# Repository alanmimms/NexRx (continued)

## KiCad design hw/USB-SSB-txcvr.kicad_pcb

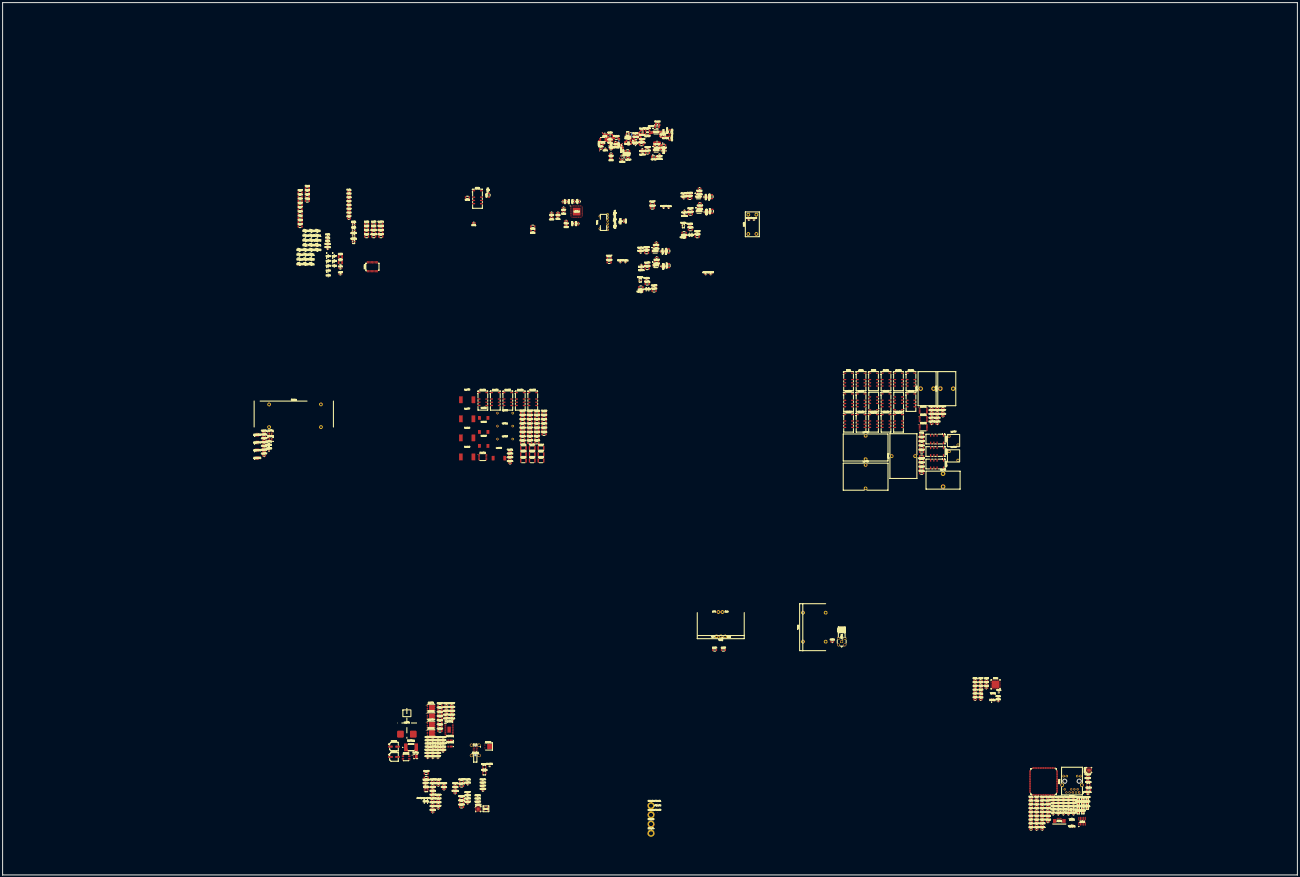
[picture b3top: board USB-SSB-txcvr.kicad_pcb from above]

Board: 6 copper layers, 1022.4 x 688.8 mm, 592 parts (0 on the bottom side), 441 nets.

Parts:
C201, C211, C1604, C1705, C2106, C2108: 100nF; C_0805_2012Metric
C202, C204, C205, C306, C308, C311, C313, C501, C1601, C1602, C1603, C1701, C1702, C1703, C1704, C1816, C1817, C1820, C1821, C2005, C2101, C2102, C2103, C2104, C2105, C2107, C2406: 10uF; C_0805_2012Metric
C203: 100uF; C_0805_2012Metric
C206, C207, C208, C210, C212, C214, C217, C218, C219, C220, C221, C222, C224, C225, C303, C307, C309, C310, C312, C314, C315, C316, C318, C321, C602, C608, C609, C613, C615, C1202, C1212, C1213, C1302, C1312, C1313, C1402, C1412, C1413, C1803, C1814, C1815, C2003, C2007, C2008, C2012, C2301, C2302, C2403, C2407, C2408, C2409, C2410, C2411: 0.1uF; C_0805_2012Metric
C209, C216, C223, C304, C320, C401, C402, C408, C410, C412, C413, C415, C417, C601, C603, C604, C1806, C1811, C1812, C1813, C1818, C1819, C2307, C2404: 1uF; C_0805_2012Metric
C213, C215, C302, C305, C2303, C2304: 2.2uF; C_0805_2012Metric
C301: 1uF 250V; C_1206_3216Metric
C317, C319, C605, C607, C612, C614, C2006, C2111, C2112: 4.7uF; C_0805_2012Metric
C403: 4pF; C_1206_3216Metric
C404: 8pF; C_1206_3216Metric
C405: 16pF; C_1206_3216Metric
C406: 32pF; C_1206_3216Metric
C407: 64pF; C_1206_3216Metric
C409: 128pF; C_1206_3216Metric
C411: 256pF; C_1206_3216Metric
C414: 512pF; C_1206_3216Metric
C416: 1024pF; C_1206_3216Metric
C418: 2048pF; C_1206_3216Metric
C419, C420, C1204, C1205, C1207, C1208, C1209, C1210, C1304, C1305, C1307, C1308, C1309, C1310, C1404, C1405, C1407, C1408, C1409, C1410, C2017, C2018, C2019, C2020, C2022: 1uF; C_1206_3216Metric
C421: 2.2nF; C_1206_3216Metric
C502: 10uF 500V; C_0805_2012Metric
C606: .1uF; C_0805_2012Metric
C610, C2001: 10nF; C_0805_2012Metric
C611: 1nF; C_0805_2012Metric
C701, C1201, C1301, C1401, C2021, C2023: 10uF; C_1206_3216Metric
C1203, C1206, C1211, C1214, C1303, C1306, C1311, C1314, C1403, C1406, C1411, C1414: 2.2uF; C_1206_3216Metric
C1215, C1216, C1217, C1218, C1315, C1316, C1317, C1318, C1415, C1416, C1417, C1418: 3.3nF; C_1206_3216Metric
C1605, C1633: 39pF; C_1206_3216Metric
C1606, C1611, C1621, C1632: 150pF; C_1206_3216Metric
C1607, C1634: 75pF; C_1206_3216Metric
C1608, C1619, C1622, C1631: 27pF; C_1206_3216Metric
C1609, C1630: 360pF; C_1206_3216Metric
C1610, C1620: 330pF; C_1206_3216Metric
C1612, C1629: 62pF; C_1206_3216Metric
C1613, C1628: 33pF; C_1206_3216Metric
C1614, C1626: 24pF; C_1206_3216Metric
C1615, C1623: 300pF; C_1206_3216Metric
C1616, C1624: 120pF; C_1206_3216Metric
C1617, C1627: 68pF; C_1206_3216Metric
C1618, C1625: 36pF; C_1206_3216Metric
C1801: 4.7uF 50V; C_0805_2012Metric
C1802: 0.1uF 50V; C_0805_2012Metric
C1804, C1805: 22uF; C_0805_2012Metric
C1807, C1808, C1809, C1810: 1uF 50V; C_0805_2012Metric
C2002, C2011: 100pF; C_0603_1608Metric
C2004, C2305, C2306: 3.3nF; C_0805_2012Metric
C2009, C2010: 0.22uF; C_0603_1608Metric
C2013: 220pF; C_0805_2012Metric
C2014, C2015: 10uF; CP_Elec_6.3x5.4
C2016: 470pF; C_0805_2012Metric
C2109: 4.7uF 50V; C_1206_3216Metric
C2110: 1280pF; C_1206_3216Metric
C2113: 640pF; C_1206_3216Metric
C2114: 320pF; C_1206_3216Metric
C2115: 0.1uF 50V; C_1206_3216Metric
C2116: 160pF; C_1206_3216Metric
C2117: 80pF; C_1206_3216Metric
C2118: 40pF; C_1206_3216Metric
C2119: 20pF; C_1206_3216Metric
C2120: 10pF; C_1206_3216Metric
C2121: 5pF; C_1206_3216Metric
C2401, C2402: 8.2pF; C_0603_1608Metric
C2405: 470pF; C_1206_3216Metric
C2412: 1000pF; C_0805_2012Metric
CF1801: 1uF; C_0805_2012Metric
D301: STS321150B100AH; Infineon_SG-WLL-2-3_0.58x0.28_P0.36mm
D2001, D2002: DFLS1200-7; DFLS12007
D2101: MMQA33VT1G; SC-74-6_1.55x2.9mm_P0.95mm
FB301: 600; L_0603_1608Metric
FB2401: BLM21AG102SN1D; L_0805_2012Metric
FID101, FID102, FID103: Fiducial; Fiducial_0.5mm_Mask2mm
IC2001: LTC3779IFE#PBF; SOP50P640X120-39N
J201: 68710814022
J202: FTSH-105-01-L-DV-K; FTSH10501LDVK
J501: SMA; RFPCSMA27F
J2101: Amphenol 10167129; 1016712900011LF
J2401: RJ45_Abracon_ARJP11A-MASA-B-A-EMU2; RJ45_Abracon_ARJP11A-MA_Horizontal
K501, K701, K702, K703, K1601, K1602, K1603, K1604, K1605, K1701, K1702, K1703, K1704, K1705, K1706, K1707, K1708, K2101, K2102, K2103, K2104, K2105, K2106, K2107, K2108, K2109: G6S-2G; Relay_DPDT_Omron_G6S-2G
L301: 1.2uH; L_0805_2012Metric
L401: 8t bifilar; L_CommonMode_Toroid_Vertical_L19.3mm_W10.8mm_Px6.35mm_Py15.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
L402: 8.2uH; L_1210_3225Metric
L403: 2.7uH; L_1210_3225Metric
L404: 820nH; L_0805_2012Metric
L405: 270nH; L_0805_2012Metric
L1601, L1604, L1616, L1620: 1.2uH; L_1812_4532Metric
L1602, L1618: 3.3uH; L_Wurth_8.4mm_sq_SMT
L1603, L1607, L1614, L1619: 3.9uH; L_Wurth_12.1mm_sq_SMT
L1605, L1615: 17.4uH; toroid-inductor-t80-2
L1606, L1610, L1617: 1.5uH; L_1812_4532Metric
L1608, L1613: 1uH; L_1812_4532Metric
L1609: 8.2uH; L_Wurth_10.9mm_sq_SMT
L1611: 19.1uH; toroid-inductor-t80-2
L1612: 4.7uH; L_Wurth_8.4mm_sq_SMT
L1701: 64uH; L_Toroid_Vertical_L35.1mm_W21.1mm_P18.50mm_Vishay_TJ6
L1702: 32uH; L_Toroid_Vertical_L35.1mm_W21.1mm_P18.50mm_Vishay_TJ6
L1703: 16uH; L_Toroid_Vertical_L35.1mm_W21.1mm_P18.50mm_Vishay_TJ6
L1704: 8uH; L_Toroid_Vertical_L26.7mm_W14.0mm_P10.16mm_Pulse_D
L1705: 4uH; L_Toroid_Vertical_L26.7mm_W14.0mm_P10.16mm_Pulse_D
L1706: 2uH; L_Toroid_Vertical_L26.7mm_W14.0mm_P10.16mm_Pulse_D
L1707: 1uH; Coilcraft-uni10
L1708: 0.5uH; Coilcraft-uni10
L1801: 2.2uH; IND_XGL4030_COC
L1802: 2.2uH; L_0805_2012Metric
L1803: 3.3uH; L_0805_2012Metric
L2001: 6.8uH; Bourns PQ2614BLA-6R8K
MH101, MH102, MH103, MH104: MountingHole; MountingHole_3.2mm_M3_ISO7380_Pad
Q801, Q901, Q1001, Q1101: 2N7002K; SOT-23
Q2001, Q2002, Q2003, Q2004: BSC360N15NS3 G; Infineon_PG-TDSON-8_6.15x5.15mm
Q2101: SQJ433EP; PowerPAK_SO-8L_Single
Q2301, Q2302: EPC2037; EPC_BGA-4_0.9x0.9mm_Layout2x2_P0.45mm
Q2303, Q2304, Q2305, Q2306: IGB110S101XTMA1
R201, R202, R203, R204, R205, R206, R207, R208, R210, R303, R304, R801, R901, R1001, R1101, R1201, R1202, R1203, R1204, R1205, R1206, R1207, R1208, R1301, R1302, R1303, R1304, R1305, R1306, R1307, R1308, R1401, R1402, R1403, R1404, R1405, R1406, R1407, R1408, R2002, R2005, R2008, R2108, R2401, R2406, R2408, R2409, R2410, R2420: 10k; R_0603_1608Metric
R209, R602, R2015, R2016, R2019, R2020, R2104: 100; R_0603_1608Metric
R301, R302, R2012, R2013, R2101, R2106: 1k; R_0603_1608Metric
R401: 6.8; R_0603_1608Metric
R501: 49.9; R_1206_3216Metric
R502, R504: 47k; R_1206_3216Metric
R503, R505: 220; R_1206_3216Metric
R601, R1805, R1806, R2411, R2412: 0; R_0603_1608Metric
R802, R804, R902, R904, R1002, R1004, R1102, R1104: 34; R_1206_3216Metric
R803, R903, R1003, R1103: 562; R_1206_3216Metric
R1209, R1210, R1211, R1212, R1309, R1310, R1311, R1312, R1409, R1410, R1411, R1412: 330; R_0603_1608Metric
R1801: 60.4k; R_0603_1608Metric
R1802, R2415: 12.1k; R_0603_1608Metric
R1803, R1804, R1811, R1812, R1813, R1814, R2105: 0; R_1206_3216Metric
R1807, R1809, R2003, R2009, R2102, R2107, R2407: 100k; R_0603_1608Metric
R1808: 22.1k; R_0603_1608Metric
R1810: 13.7k; R_0603_1608Metric
R2001: 649k; R_0603_1608Metric
R2004, R2010: 3.53k; R_0603_1608Metric
R2006: 13k; R_0603_1608Metric
R2007: 125k; R_0603_1608Metric
R2011: 107k; R_0603_1608Metric
R2014: 5; R_0603_1608Metric
R2017, R2018, R2022, R2023: 2; R_0603_1608Metric
R2021: 5m; CSS2H3920K5L00F
R2103: 22k; R_0603_1608Metric
R2402, R2403, R2404, R2405: 33; R_0603_1608Metric
R2413, R2414, R2416, R2417: 49.9; R_0603_1608Metric
R2418, R2419: 270; R_0805_2012Metric
T301: 12t primary : 6T #26 trifilar secondary FT37-43; Toroid-1pri-3sec-ft50
T501: 2xFT140-stacked-bruene
T502: 16t:8t bifilar #18AWG FT140-43; 2xFT140-stacked
T2301: 2xFT240-stacked
TP201: PG0; TestPoint_Pad_1.5x1.5mm
TP202: PG1; TestPoint_Pad_1.5x1.5mm
TP203: PG2; TestPoint_Pad_1.5x1.5mm
TP204: PG3; TestPoint_Pad_1.5x1.5mm
TP205: PG4; TestPoint_Pad_1.5x1.5mm
TP206: PG5; TestPoint_Pad_1.5x1.5mm
TP207: PG6; TestPoint_Pad_1.5x1.5mm
TP208: PG7; TestPoint_Pad_1.5x1.5mm
TP209: PG8; TestPoint_Pad_1.5x1.5mm
TP210: PG14; TestPoint_Pad_1.5x1.5mm
TP211: PG15; TestPoint_Pad_1.5x1.5mm
U201: STM32H753ZIT6; LQFP-144_20x20mm_P0.5mm
U301: OPA1692xDGK; VSSOP-8_3x3mm_P0.65mm
U302, U303, U304, U410, U411, U412, U413, U414, U415, U416, U417, U418, U419, U420, U421, U422, U423, U424, U425, U426, U801, U802, U901, U902, U1001, U1002, U1101, U1102: AS183-92LF; SOT65P220X110-6N
U305: SOT65P220X110-6N
U306: AK5578EN; QFN50P900X900X100-65N
U401: MCP23S17_SS; SSOP-28_5.3x10.2mm_P0.65mm
U402, U403, U404, U405, U406, U407, U408, U409: 74LVC2G04; DCK6
U601: TPS7A2025PDQN; Texas_X2SON-4_1x1mm_P0.65mm
U602: ICE40UP5K-SG48ITR; QFN-48-1EP_7x7mm_P0.5mm_EP5.6x5.6mm
U1201, U1301, U1401: SZNUP1105LT1G; SOT-23
U1202, U1302, U1402: TS3A4751RUCR; TS3A4751-RUC14
U1203, U1204, U1303, U1304, U1403, U1404: MAX9939AUB+T; 21-0061L_MXM
U1601, U1701, U2101, U2102: TLC6C598PW; TSSOP-16_4.4x5mm_P0.65mm
U1801: LMR43610R3RPER; RPE0009A-MFG
U1802: TPS7A2012DQN; Texas_X2SON-4_1x1mm_P0.65mm
U1803, U1804: LMR51430; SOT-23-6
U1805: TPS7A92050DBVR; Texas_X2SON-4_1x1mm_P0.65mm
U1806: TPS7A2033DQN; Texas_X2SON-4_1x1mm_P0.65mm
U2001: NVTFS6H888NLTAG; WDFN_8NLTAG_ONS
U2002: TLV9062xD; SOIC-8_3.9x4.9mm_P1.27mm
U2103: STUSB4500QTR; QFN-24-1EP_4x4mm_P0.5mm_EP2.7x2.7mm
U2301, U2302: LMG1210RVRR; RVR0019A
U2303: TMP110D; Texas_X2SON-5_0.8x0.8mm_P0.48mm
U2401: LAN8742A; VQFN-24-1EP_4x4mm_P0.5mm_EP2.5x2.5mm_ThermalVias
U2402: USBLC6-4SC6; SOT-23-6
X601: XC8102AA01NR-G; XC8102AA01NRG
Y201: ECS-2033-250-BN; ECS2033250BN
Y601: ECS-TXO-2016-33-400-TR; ECSTXO201633400TR
Y2401: ECS-250-8-37B2-RWN; ECS2033250BN

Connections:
+2.7V: C2112.1, U2103.23 (VREG_2V7)
+3.3V: C201.1, C202.1, C203.1, C204.1, C205.1, C206.1, C207.1, C208.1, C210.1, C212.1, C214.1, C216.1, C217.1, C218.1, C219.1, C220.1, C221.1, C222.1, C224.1, C315.1, C316.2, C317.2, C320.1, C321.1, C401.1, C402.1, C408.1, C410.1, C412.1, C413.1, C415.1, C417.1, C419.1, C420.1, C601.1, C602.1, C603.1, C1603.2, C1604.2, C1704.2, C1705.2, C1806.1, C2104.2, C2106.2, C2107.2, C2108.2, C2307.1, C2403.1, FB2401.1, J201.2, J201.8, J202.1 (VTref), R202.1, R203.1, R204.1, R205.1, R206.1, R207.1, R208.1, R601.1, R801.1, R901.1, R1001.1, R1101.1, R1805.1, R1806.1, R1813.1, R2005.1, R2108.1, R2406.2, R2407.2, R2408.2, R2409.2, R2410.2, U201.6 (VBAT), U201.17 (VDD), U201.30 (VDD), U201.39 (VDD), U201.52 (VDD), U201.62 (VDD), U201.72 (VDD), U201.84 (VDD), U201.95 (VDD33USB), U201.108 (VDD), U201.121 (VDD), U201.131 (VDD), U201.144 (VDD), U305.5 (V), U306.25 (TVDD), U306.30 (PW1), U306.31 (PW2), U306.32 (MSN), U306.51 (TDM0), U306.52 (TDM1), U306.54 (I2C), U306.57 (LDOE), U306.58 (ODP), U401.9 (VDD), U401.15 (A0), U402.5 (V), U403.5 (V), U404.5 (V), U405.5 (V), U406.5 (V), U407.5 (V), U408.5 (V), U409.5 (V), U601.4 (IN), U1601.1 (VCC), U1601.7 (~CLR), U1601.8 (~G), U1701.1 (VCC), U1701.7 (~CLR), U1701.8 (~G), U1802.4 (IN), U2101.1 (VCC), U2101.7 (~CLR), U2101.8 (~G), U2102.1 (VCC), U2102.7 (~CLR), U2102.8 (~G), U2303.5 (V+), U2401.9 (VDDIO), Y201.4 (VDD), Y601.4 (VDD)
+3.3VA: C223.1, C225.1, C1201.1, C1202.1, C1301.1, C1302.1, C1401.1, C1402.1, R301.2, R1812.1, U201.33 (VDDA), U1201.3, U1202.14 (V+), U1301.3, U1302.14 (V+), U1401.3, U1402.14 (V+)
+3.3VFPGAIO: C605.1, C606.1, C612.1, C613.1, C614.1, C615.1, U602.1 (VCCIO_2), U602.22 (SPI_VCCIO1), U602.33 (VCCIO_0), X601.3 (VOUT)
+5V: C501.1, C701.2, C1601.1, C1602.1, C1701.1, C1702.1, C1703.1, C2101.1, C2102.1, C2103.1, C2105.2, C2301.1, C2302.1, C2303.1, C2304.1, K501.12, K701.1, K702.1, K703.1, K1601.1, K1602.1, K1603.1, K1604.1, K1605.1, K1701.1, K1702.1, K1703.1, K1704.1, K1705.1, K1706.1, K1707.1, K1708.1, K2101.1, K2102.1, K2103.1, K2104.1, K2105.1, K2106.1, K2107.1, K2108.1, K2109.1, Q2301.2 (S), Q2301.4 (S), Q2302.2 (S), Q2302.4 (S), R1814.1, U2301.2 (VIN), U2301.4 (VCC), U2301.5 (DHL), U2301.6 (DLH), U2302.2 (VIN), U2302.4 (VCC), U2302.5 (DHL), U2302.6 (DLH)
+5VA: C309.1, C1209.1, C1210.1, C1212.1, C1213.1, C1309.1, C1310.1, C1312.1, C1313.1, C1409.1, C1410.1, C1412.1, C1413.1, C2001.1, C2003.1, C2005.1, R1811.1, U301.8 (V+), U306.2 (AVDD1), U306.15 (AVDD2), U1203.9 (VCC), U1204.9 (VCC), U1303.9 (VCC), U1304.9 (VCC), U1403.9 (VCC), U1404.9 (VCC), U2002.8 (V+)
+6V: C1812.1, C1813.1, R1803.1, U1805.4 (IN), U1806.4 (IN)
/FPGA/CDONE: U201.141 (PE0), U602.7 (CDONE)
/FPGA/Ctrl.audioReset: R210.1, U201.42 (PA6), U306.28 (PDN)
/FPGA/Ctrl.enable5V: U201.26 (PC0), U1804.5 (EN)
/FPGA/Ctrl.enable6V: U201.53 (PF13), U1801.3 (EN_UVLO)
/FPGA/Ctrl.qsdBCLK: U201.4 (PE5), U306.33 (BICK/DCLK)
/FPGA/Ctrl.qsdData: U201.5 (PE6), U306.36 (SDTO1/DSDOL2)
/FPGA/Ctrl.qsdMCLK: U306.24 (MCLK), U602.12 (IOB_22a)
/FPGA/Ctrl.qsdMOSI: U201.67 (PE14), U1203.2 (DIN), U1204.2 (DIN), U1303.2 (DIN), U1304.2 (DIN), U1403.2 (DIN), U1404.2 (DIN)
/FPGA/Ctrl.qsdNSS: U201.64 (PE11), U1203.10 (*CS), U1204.10 (*CS), U1303.10 (*CS), U1304.10 (*CS), U1403.10 (*CS), U1404.10 (*CS)
/FPGA/Ctrl.qsdPh0a: U602.6 (IOB_13b), U1402.1 (NO1)
/FPGA/Ctrl.qsdPh1a: U602.21 (IOB_23b), U1202.1 (NO1)
/FPGA/Ctrl.qsdPh2a: U602.45 (IOB_5b), U1302.1 (NO1)
/FPGA/Ctrl.qsdPh2b: U602.2 (IOB_6a), U602.9 (IOB_16a), U602.13 (IOB_24a), U1202.3 (NO2), U1302.3 (NO2), U1402.3 (NO2)
/FPGA/Ctrl.qsdPh2c: U602.4 (IOB_8a), U602.10 (IOB_18a), U602.20 (IOB_25b_G3), U1202.8 (NO3), U1302.8 (NO3), U1402.8 (NO3)
/FPGA/Ctrl.qsdPh2d: U602.3 (IOB_9b), U602.11 (IOB_20a), U602.19 (IOB_29b), U1202.11 (NO4), U1302.11 (NO4), U1402.11 (NO4)
/FPGA/Ctrl.qsdSCK: U201.1 (PE2), U1203.1 (SCLK), U1204.1 (SCLK), U1303.1 (SCLK), U1304.1 (SCLK), U1403.1 (SCLK), U1404.1 (SCLK)
/FPGA/Ctrl.qsdWCLK: U201.3 (PE4), U306.34 (LRCK/DSDOL1)
/FPGA/Ctrl.switchMOSI: U201.29 (PC3_C), U2101.2 (SER_IN)
/FPGA/Ctrl.switchRCK: U201.10 (PF0), U1601.10 (RCK), U1701.10 (RCK), U2101.10 (RCK), U2102.10 (RCK)
/FPGA/Ctrl.switchSCK: U201.69 (PB10), U1601.15 (SRCK), U1701.15 (SRCK), U2101.15 (SRCK), U2102.15 (SRCK)
/FPGA/Ctrl.tmpSCL: U201.136 (PB6), U2103.7 (SCL)
/FPGA/Ctrl.tmpSDA: U201.137 (PB7), U2103.8 (SDA)
/FPGA/Ctrl.txBCLK: U201.20 (PF8), U602.43 (IOT_49a)
/FPGA/Ctrl.txData: U201.2 (PE3), U602.42 (IOT_51a)
/FPGA/Ctrl.txMCLK: U201.19 (PF7), U602.36 (IOT_48b)
/FPGA/Ctrl.txWCLK: U201.21 (PF9), U602.38 (IOT_50b)
/FPGA/Ctrl.usbPOK2: U201.22 (PF10), U2103.20 (POWER_OK2)
/FPGA/Ctrl.usbPOK3: U201.49 (PF11), U2103.14 (POWER_OK3)
/FPGA/Ctrl.usbReset: R2107.1, U2103.6 (RESET)
/FPGA/Ctrl.usbnALERT: R2108.2, U201.54 (PF14), U2103.19 (ALERT)
/FPGA/PAI+: U602.25 (IOT_36b), U2301.18 (HI_EN)
/FPGA/PAI-: U602.23 (IOT_37a), U2301.19 (PWM_LI)
/FPGA/PAQ+: U602.27 (IOT_38b), U2302.18 (HI_EN)
/FPGA/PAQ-: U602.26 (IOT_39a), U2302.19 (PWM_LI)
/FPGA/STM32clock: U201.23 (PH0-OSC_IN), U602.18 (IOB_31b)
/Power/FPGA1V2enable: U201.142 (PE1), U1802.3 (EN)
/Power/Tx EER Envelope Buck-Boost/BG1: IC2001.1 (BG1), R2018.1
/Power/Tx EER Envelope Buck-Boost/BG2: IC2001.19 (BG2), R2023.1
/Power/Tx EER Envelope Buck-Boost/FB: C2011.2, IC2001.10 (VFB), R2011.2, U2002.1
/Power/Tx EER Envelope Buck-Boost/IAVGSNSN: C2016.2, R2019.1
/Power/Tx EER Envelope Buck-Boost/IAVGSNSP: C2016.1, IC2001.26 (IAVGSNSP), IC2001.28 (IAVGSNSN), R2020.1
/Power/Tx EER Envelope Buck-Boost/SENSEN: C2013.1, IC2001.12 (SENSEN), R2016.1
/Power/Tx EER Envelope Buck-Boost/SENSEP: C2013.2, IC2001.11 (SENSEP), R2015.1
/Power/Tx EER Envelope Buck-Boost/SW1: C2010.1, IC2001.38 (SW1), L2001.1, Q2001.1 (S), Q2001.2 (S), Q2001.3 (S), Q2002.5 (D)
/Power/Tx EER Envelope Buck-Boost/SW2: C2009.2, IC2001.20 (SW2), L2001.2, Q2003.1 (S), Q2003.2 (S), Q2003.3 (S), Q2004.5 (D)
/Power/Tx EER Envelope Buck-Boost/TG1: IC2001.37 (TG1), R2017.1
/Power/Tx EER Envelope Buck-Boost/TG2: IC2001.21 (TG2), R2022.1
/Power/TxAmplitude: R2008.1, U201.40 (PA4)
/Power/TxEnable: IC2001.24 (RUN), U201.103 (PA11)
/Power/TxPGOOD: IC2001.18 (PGOOD), R2005.2, U201.96 (PC6)
/Power/USB-PD/CC1: D2101.4 (K_3), J2101.A5 (CC1), U2103.1 (CC1DB), U2103.2 (CC1)
/Power/USB-PD/CC2: D2101.6 (K_4), J2101.B5 (CC2), U2103.4 (CC2), U2103.5 (CC2DB)
/Power/USB-PD/VBUS_DISCH: R2101.2, U2103.18 (VBUS_VS_DISCH)
/Power/scaledEERVdd: U201.50 (PF12), U2002.6 (-), U2002.7
/Rx Front End/Clipper, Attenuator, Preselector/C0: U401.21 (GPA0), U406.1, U410.4 (V1)
/Rx Front End/Clipper, Attenuator, Preselector/C1: U401.22 (GPA1), U406.3, U411.4 (V1)
/Rx Front End/Clipper, Attenuator, Preselector/C2: U401.23 (GPA2), U407.1, U412.4 (V1)
/Rx Front End/Clipper, Attenuator, Preselector/C3: U401.24 (GPA3), U407.3, U413.4 (V1)
/Rx Front End/Clipper, Attenuator, Preselector/C4: U401.25 (GPA4), U408.1, U414.4 (V1)
/Rx Front End/Clipper, Attenuator, Preselector/C5: U401.26 (GPA5), U408.3, U416.4 (V1)
/Rx Front End/Clipper, Attenuator, Preselector/C6: U401.27 (GPA6), U409.1, U417.4 (V1)
/Rx Front End/Clipper, Attenuator, Preselector/C7: U401.28 (GPA7), U409.3, U419.4 (V1)
/Rx Front End/Clipper, Attenuator, Preselector/C8: U401.1 (GPB0), U402.1, U422.4 (V1)
/Rx Front End/Clipper, Attenuator, Preselector/C9: U401.2 (GPB1), U402.3, U424.4 (V1)
/Rx Front End/Clipper, Attenuator, Preselector/C10: U401.3 (GPB2), U403.1, U426.4 (V1)
/Rx Front End/Clipper, Attenuator, Preselector/Ctrl.atten3dB: Q1101.1 (G), U1101.4 (V1), U1102.4 (V1)
/Rx Front End/Clipper, Attenuator, Preselector/Ctrl.atten6dB: Q801.1 (G), U801.4 (V1), U802.4 (V1)
/Rx Front End/Clipper, Attenuator, Preselector/Ctrl.atten12dB: Q901.1 (G), U901.4 (V1), U902.4 (V1)
/Rx Front End/Clipper, Attenuator, Preselector/Ctrl.atten24dB: Q1001.1 (G), U1001.4 (V1), U1002.4 (V1)
/Rx Front End/Clipper, Attenuator, Preselector/L1: U401.5 (GPB4), U404.1, U418.4 (V1)
/Rx Front End/Clipper, Attenuator, Preselector/L1L2: U401.4 (GPB3), U403.3, U415.4 (V1), U421.4 (V1)
/Rx Front End/Clipper, Attenuator, Preselector/L2: U401.6 (GPB5), U404.3, U420.4 (V1)
/Rx Front End/Clipper, Attenuator, Preselector/L3: U401.7 (GPB6), U405.1, U423.4 (V1)
/Rx Front End/Clipper, Attenuator, Preselector/L4: U401.8 (GPB7), U405.3, U425.4 (V1)
/Rx Front End/Clipper, Attenuator, Preselector/RxZ200: C301.2, D301.1 (A1), U1001.5 (J1)
/Rx Front End/Clipper, Attenuator, Preselector/Tpad 3/in: U802.5 (J1), U1101.5 (J1)
/Rx Front End/Clipper, Attenuator, Preselector/Tpad 3/nEn: Q1101.3 (D), R1101.2, U1101.6 (V2), U1102.6 (V2)
/Rx Front End/Clipper, Attenuator, Preselector/Tpad 3/out: L401.1, U1102.5 (J1)
/Rx Front End/Clipper, Attenuator, Preselector/Tpad 6/nEn: Q801.3 (D), R801.2, U801.6 (V2), U802.6 (V2)
/Rx Front End/Clipper, Attenuator, Preselector/Tpad 12/in: U901.5 (J1), U1002.5 (J1)
/Rx Front End/Clipper, Attenuator, Preselector/Tpad 12/nEn: Q901.3 (D), R901.2, U901.6 (V2), U902.6 (V2)
/Rx Front End/Clipper, Attenuator, Preselector/Tpad 12/out: U801.5 (J1), U902.5 (J1)
/Rx Front End/Clipper, Attenuator, Preselector/Tpad 24/nEn: Q1001.3 (D), R1001.2, U1001.6 (V2), U1002.6 (V2)
/Rx Front End/Clipper, Attenuator, Preselector/nC0: U406.6, U410.6 (V2)
/Rx Front End/Clipper, Attenuator, Preselector/nC1: U406.4, U411.6 (V2)
/Rx Front End/Clipper, Attenuator, Preselector/nC2: U407.6, U412.6 (V2)
/Rx Front End/Clipper, Attenuator, Preselector/nC3: U407.4, U413.6 (V2)
/Rx Front End/Clipper, Attenuator, Preselector/nC4: U408.6, U414.6 (V2)
/Rx Front End/Clipper, Attenuator, Preselector/nC5: U408.4, U416.6 (V2)
/Rx Front End/Clipper, Attenuator, Preselector/nC6: U409.6, U417.6 (V2)
/Rx Front End/Clipper, Attenuator, Preselector/nC7: U409.4, U419.6 (V2)
/Rx Front End/Clipper, Attenuator, Preselector/nC8: U402.6, U422.6 (V2)
/Rx Front End/Clipper, Attenuator, Preselector/nC9: U402.4, U424.6 (V2)
/Rx Front End/Clipper, Attenuator, Preselector/nC10: U403.6, U426.6 (V2)
/Rx Front End/Clipper, Attenuator, Preselector/nL1: U404.6, U418.6 (V2)
/Rx Front End/Clipper, Attenuator, Preselector/nL1L2: U403.4, U415.6 (V2), U421.6 (V2)
/Rx Front End/Clipper, Attenuator, Preselector/nL2: U404.4, U420.6 (V2)
/Rx Front End/Clipper, Attenuator, Preselector/nL3: U405.6, U423.6 (V2)
/Rx Front End/Clipper, Attenuator, Preselector/nL4: U405.4, U425.6 (V2)
/Rx Front End/Clipper, Attenuator, Preselector/rxPreselOut: L401.3, T301.1 (IN+), U410.1 (J3), U411.1 (J3), U412.1 (J3), U413.1 (J3), U414.1 (J3), U416.1 (J3), U417.1 (J3), U418.3 (J2), U419.1 (J3), U420.3 (J2), U422.1 (J3), U423.3 (J2), U424.1 (J3), U425.3 (J2), U426.1 (J3)
/Rx Front End/Ctrl.breune: U302.6 (V2), U303.6 (V2), U304.6 (V2), U305.1
/Rx Front End/QSD0/rfIn: U302.5 (J1), U1401.1, U1402.5 (IN2), U1402.6 (IN3), U1402.12 (IN4), U1402.13 (IN1)
/Rx Front End/QSD1/rfIn: U303.5 (J1), U1201.1, U1202.5 (IN2), U1202.6 (IN3), U1202.12 (IN4), U1202.13 (IN1)
/Rx Front End/QSD2/rfIn: U304.5 (J1), U1301.1, U1302.5 (IN2), U1302.6 (IN3), U1302.12 (IN4), U1302.13 (IN1)
/Rx Front End/RxI0n: C1416.1, R1410.2
/Rx Front End/RxI0p: C1415.1, R1409.2, U306.59 (AIN1P)
/Rx Front End/RxI1n: C1216.1, R1210.2, U306.4 (AIN3N)
/Rx Front End/RxI1p: C1215.1, R1209.2, U306.3 (AIN3P)
/Rx Front End/RxI2n: C1316.1, R1310.2, U306.10 (AIN5N)
/Rx Front End/RxI2p: C1315.1, R1309.2, U306.9 (AIN5P)
/Rx Front End/RxQ0n: C1418.1, R1412.2
/Rx Front End/RxQ0p: C1417.1, R1411.2, U306.64 (AIN2P)
/Rx Front End/RxQ1n: C1218.1, R1212.2, U306.7 (AIN4N)
/Rx Front End/RxQ1p: C1217.1, R1211.2, U306.8 (AIN4P)
/Rx Front End/RxQ2n: C1318.1, R1312.2, U306.13 (AIN6N)
/Rx Front End/RxQ2p: C1317.1, R1311.2, U306.14 (AIN6P)
/Rx Front End/RxZ200: C301.1, K501.10
/Rx Front End/VREF1: C306.1, C307.1, U306.62 (VREFH1)
/Rx Front End/VREF2: C308.1, C310.1, U306.6 (VREFH2)
/Rx Front End/VREF3: C311.1, C312.1, U306.11 (VREFH3)
/Rx Front End/VREF4: C313.1, C314.1, U306.19 (VREFH4)
/Rx Front End/nBruene: U302.4 (V1), U303.4 (V1), U304.4 (V1), U305.6
/Rx Front End/txFwd: R502.2, R503.1, U302.1 (J3), U304.1 (J3)
/Rx Front End/txRev: R504.2, R505.1, U303.1 (J3)
/Tx Chain/Antenna Tuner/Tuner Capacitors/Ccold: K702.9, K2101.8, K2101.10, K2102.8, K2102.10, K2103.8, K2103.10, K2104.8, K2104.10, K2105.8, K2105.10, K2106.8, K2106.10, K2107.8, K2107.10, K2108.8, K2108.10, K2109.8, K2109.10
/Tx Chain/Antenna Tuner/Tuner Capacitors/Chot: K702.4, K2101.5, K2102.5, K2103.5, K2104.5, K2105.5, K2106.5, K2107.5, K2108.5, K2109.5
/Tx Chain/Antenna Tuner/Tuner Capacitors/bypass: K701.12, U2102.6 (DRAIN3)
/Tx Chain/Antenna Tuner/Tuner Capacitors/config1: K702.12, U2102.4 (DRAIN1)
/Tx Chain/Antenna Tuner/Tuner Capacitors/config2: K703.12, U2102.5 (DRAIN2)
/Tx Chain/Antenna Tuner/Tuner Capacitors/serOut: U1701.2 (SER_IN), U2102.9 (SER_OUT)
/Tx Chain/Antenna Tuner/Tuner Inductors/Lcold: K703.9, K1701.8, K1701.10, K1702.8, K1702.10, K1703.8, K1703.10, K1704.8, K1704.10, K1705.8, K1705.10, K1706.8, K1706.10, K1707.8, K1707.10, K1708.8, K1708.10
/Tx Chain/Antenna Tuner/Tuner Inductors/Lhot: K703.4, K1701.5, K1702.5, K1703.5, K1704.5, K1705.5, K1706.5, K1707.5, K1708.5
/Tx Chain/Antenna Tuner/ant: K701.3, K702.5, K702.10, K703.3, K703.8, T502.1
/Tx Chain/Antenna Tuner/rig: K701.4, K702.3, K703.5, T501.2
/Tx Chain/Antenna Tuner/txRelay: K501.1, U2102.14 (DRAIN7)
/Tx Chain/H-bridge-PA/PA200: K501.4, K501.8, T2301.3
/Tx Chain/Tx LPFs/PA200tx: K501.5, K501.9, K1601.3, K1602.5, K1603.3, K1604.3, K1605.3
/Tx Chain/Tx LPFs/TxOut: K1601.10, K1602.10, K1603.10, K1604.10, K1605.10, T501.1
/Tx Chain/tunerSerOut: U1601.2 (SER_IN), U1701.9 (SER_OUT)
/microcontroller/BOOT0: R201.1, U201.138 (BOOT0)
/microcontroller/Ctrl.audioSCL: R202.2, U201.81 (PD12)
/microcontroller/Ctrl.audioSDA: R204.2, U201.55 (PF15)
/microcontroller/EthCLK: R2402.1, U201.35 (PA1)
/microcontroller/EthCRS_DV: R2405.1, U201.43 (PA7)
/microcontroller/EthMDC: U201.27 (PC1), U2401.13 (MDC)
/microcontroller/EthMDIO: R2407.1, U201.36 (PA2), U2401.12 (MDIO)
/microcontroller/EthRXD1: R2404.1, U201.45 (PC5)
/microcontroller/EthTXD0: U201.128 (PG13), U2401.17 (TXD0)
/microcontroller/EthTXD1: U201.127 (PG12), U2401.18 (TXD1)
/microcontroller/EthTxEnable: U201.126 (PG11), U2401.16 (TXEN)
/microcontroller/Ethernet/EthRx+: J2401.3 (RD+), R2416.2, U2401.23 (RXP), U2402.1 (I/O1)
/microcontroller/Ethernet/EthRx-: J2401.6 (RD-), R2417.2, U2401.22 (RXN), U2402.6 (I/O4)
/microcontroller/Ethernet/EthTx+: J2401.1 (TD+), R2413.2, U2401.21 (TXP), U2402.3 (I/O2)
/microcontroller/Ethernet/EthTx-: J2401.2 (TD-), R2414.2, U2401.20 (TXN), U2402.4 (I/O3)
/microcontroller/Ethernet/LEDGA: J2401.13, R2420.1, U2401.2 (LED2/~INTSEL)
/microcontroller/Ethernet/LEDYA: J2401.11, U2401.3 (LED1/REGOFF)
/microcontroller/SWCL: J202.4 (SWCLK/TCK), U201.109 (PA14)
/microcontroller/SWDIO: J202.2 (SWDIO/TMS), U201.105 (PA13)
/microcontroller/SWO: J202.6 (SWO/TDO), U201.133 (PB3)
/microcontroller/VREF: C209.1, C211.1, U201.32 (VREF+)
/microcontroller/dispDC: J201.5, U201.66 (PE13)
/microcontroller/dispMOSI: J201.4, U201.123 (PD7)
/microcontroller/dispNSS: J201.1, U201.125 (PG10)
/microcontroller/dispRESET: J201.6, U201.65 (PE12)
/microcontroller/dispSCK: J201.3, U201.41 (PA5)
FPGA1V2: C608.2, C610.2, C611.2, R602.1, R1804.1, U602.5 (VCC), U602.30 (VCC)
GND: C201.2, C202.2, C203.2, C204.2, C205.2, C206.2, C207.2, C208.2, C209.2, C210.2, C211.2, C212.2, C213.2, C214.2, C215.2, C216.2, C217.2, C218.2, C219.2, C220.2, C221.2, C222.2, C223.2, C224.2, C225.2, C302.2, C303.2, C304.1, C305.2, C306.2, C307.2, C308.2, C309.2, C310.2, C311.2, C312.2, C313.2, C314.2, C315.2, C316.1, C317.1, C318.1, C319.1, C320.2, C321.2, C401.2, C402.2, C403.2, C404.2, C405.2, C406.2, C407.2, C408.2, C409.2, C410.2, C411.2, C412.2, C413.2, C414.2, C415.2, C416.2, C417.2, C418.2, C419.2, C420.2, C421.2, C501.2, C601.2, C602.2, C603.2, C604.2, C605.2, C606.2, C607.1, C608.1, C609.1, C610.1, C611.1, C612.2, C613.2, C614.2, C615.2, C701.1, C1201.2, C1202.2, C1203.2, C1206.2, C1209.2, C1210.2, C1211.2, C1212.2, C1213.2, C1214.2, C1215.2, C1216.2, C1217.2, C1218.2, C1301.2, C1302.2, C1303.2, C1306.2, C1309.2, C1310.2, C1311.2, C1312.2, C1313.2, C1314.2, C1315.2, C1316.2, C1317.2, C1318.2, C1401.2, C1402.2, C1403.2, C1406.2, C1409.2, C1410.2, C1411.2, C1412.2, C1413.2, C1414.2, C1415.2, C1416.2, C1417.2, C1418.2, C1601.2, C1602.2, C1603.1, C1604.1, C1605.2, C1606.2, C1607.2, C1608.2, C1609.2, C1610.2, C1611.2, C1612.2, C1613.2, C1614.2, C1615.2, C1616.2, C1617.2, C1618.2, C1619.2, C1620.2, C1621.2, C1622.2, C1623.2, C1624.2, C1625.2, C1626.2, C1627.2, C1628.2, C1629.2, C1630.2, C1631.2, C1632.2, C1633.2, C1634.2, C1701.2, C1702.2, C1703.2, C1704.1, C1705.1, C1801.2, C1802.2, C1804.2, C1805.2, C1806.2, C1807.2, C1808.2, C1809.2, C1810.2, C1811.2, C1812.2, C1813.2, C1816.2, C1817.2, C1818.2, C1819.2, C1820.2, C1821.2, C2001.2, C2002.2, C2003.2, C2004.2, C2005.2, C2006.2, C2007.2, C2008.2, C2012.1, C2014.2, C2015.2, C2017.2, C2018.2, C2019.2, C2020.2, C2021.2, C2022.2, C2023.2, C2101.2, C2102.2, C2103.2, C2104.1, C2105.1, C2106.1, C2107.1, C2108.1, C2109.2, C2111.2, C2112.2, C2301.2, C2302.2, C2303.2, C2304.2, C2307.2, C2401.1, C2402.1, C2403.2, C2404.2, C2405.2, C2406.2, C2407.2, C2408.2, C2409.2, C2410.1, C2410.2, C2411.1, C2411.2, C2412.2, CF1801.2, D301.2 (A2), D2101.2 (A_1), D2101.5 (A_2), IC2001.4 (SGND_1), IC2001.5 (EXTVCC), IC2001.14 (SGND_2), IC2001.16 (PLLIN), IC2001.23 (NP_1), IC2001.25 (NP_2), IC2001.27 (NP_3), IC2001.29 (NP_4), IC2001.31 (NP_5), IC2001.33 (NP_6), IC2001.35 (NP_7), IC2001.39 (PGND), J201.7, J201.MP1, J201.MP2, J202.3 (GND), J202.5 (GND), J202.9 (GNDDetect), J501.2 (Ext), J501.3 (Ext), J501.4 (Ext), J501.5 (Ext), J2101.1 (MH1), J2101.2 (MH2), J2101.3 (MH3), J2101.4 (MH4), J2101.A1 (GND_1), J2101.A12 (GND_2), J2101.B1 (GND_3), J2101.B12 (GND_4), J2401.4 (TCT), J2401.5 (RCT), J2401.SH, K702.8, K703.10, K1601.5, K1601.8, K1602.3, K1602.8, K1603.5, K1603.8, K1604.5, K1604.8, K1605.5, K1605.8, L401.2, L401.4, L404.2, L405.2, MH101.1, MH102.1, MH103.1, MH104.1, Q801.2 (S), Q901.2 (S), Q1001.2 (S), Q1101.2 (S), R201.2, R210.2, R302.1, R401.2, R501.2, R503.2, R505.2, R803.2, R903.2, R1003.2, R1103.2, R1201.2, R1202.2, R1203.2, R1204.2, R1301.2, R1302.2, R1303.2, R1304.2, R1401.2, R1402.2, R1403.2, R1404.2, R1802.1, R1808.1, R1810.1, R2002.2, R2004.1, R2007.2, R2010.1, R2021.1, R2107.2, R2401.1, R2415.1, R2418.2, R2419.2, R2420.2, T301.2 (IN-), T501.3, T502.2, T502.4, T2301.4, U201.8 (PC14-OSC32_IN), U201.16 (VSS), U201.31 (VSSA), U201.38 (VSS), U201.51 (VSS), U201.61 (VSS), U201.83 (VSS), U201.94 (VSS), U201.107 (VSS), U201.120 (VSS), U201.130 (VSS), U301.4 (V-), U302.2 (GND), U303.2 (GND), U304.2 (GND), U305.2 (G), U306.1 (AVSS1), U306.5 (VREFL2), U306.12 (VREFL3), U306.16 (AVSS2), U306.20 (VREFL4), U306.26 (DVSS), U306.29 (PW0), U306.44 (CKS1/CAD0_I2C/CSN), U306.46 (CKS3/CAD1), U306.47 (SLOW/DCKB), U306.48 (SD/PMOD), U306.49 (DIF0/DSDSEL0), U306.50 (DIF1/DSDSEL1), U306.53 (PSN/CAD0_SP1), U306.55 (DP), U306.56 (DCKS/HPFE), U306.60 (AIN1N), U306.61 (VREFL1), U306.63 (AIN2N), U306.65 (THERMAL_PAD), U401.10 (VSS), U401.16 (A1), U401.17 (A2), U402.2 (G), U403.2 (G), U404.2 (G), U405.2 (G), U406.2 (G), U407.2 (G), U408.2 (G), U409.2 (G), U410.2 (GND), U410.3 (J2), U411.2 (GND), U411.3 (J2), U412.2 (GND), U412.3 (J2), U413.2 (GND), U413.3 (J2), U414.2 (GND), U414.3 (J2), U415.1 (J3), U415.2 (GND), U416.2 (GND), U416.3 (J2), U417.2 (GND), U417.3 (J2), U419.2 (GND), U419.3 (J2), U420.1 (J3), U421.1 (J3), U421.2 (GND), U422.2 (GND), U422.3 (J2), U423.1 (J3), U424.2 (GND), U424.3 (J2), U425.1 (J3), U425.2 (GND), U426.2 (GND), U426.3 (J2), U601.2 (GND), U601.5 (Pad), U602.49 (GND), U801.2 (GND), U802.2 (GND), U901.2 (GND), U902.2 (GND), U1001.2 (GND), U1002.2 (GND), U1101.2 (GND), U1102.2 (GND), U1201.2, U1202.7 (GND), U1203.3 (GND), U1204.3 (GND), U1301.2, U1302.7 (GND), U1303.3 (GND), U1304.3 (GND), U1401.2, U1402.7 (GND), U1403.3 (GND), U1404.3 (GND), U1601.16 (GND), U1701.16 (GND), U1801.1 (MODE_SYNC), U1801.9 (GND), U1802.2 (GND), U1802.5 (Pad), U1803.1 (GND), U1804.1 (GND), U1805.2 (GND), U1805.5 (Pad), U1806.2 (GND), U1806.5 (Pad), U2002.4 (V-), U2101.16 (GND), U2102.16 (GND), U2103.3 (NU), U2103.10 (GND), U2103.12 (ADDR0), U2103.13 (ADDR1), U2103.22 (VSYS), U2103.25 (GND), U2301.3 (VSS), U2301.7 (VSS), U2301.20 (LS_DAP), U2302.3 (VSS), U2302.7 (VSS), U2302.20 (LS_DAP), U2303.1 (GND), U2303.3 (ADD0), U2401.25 (VSS), U2402.2 (GND), X601.2 (VSS_), Y201.2 (GROUND), Y601.2 (GND), Y2401.2, Y2401.4
unnamed: C303.1, C305.1, L301.2, R304.1
unnamed: C502.1, T502.3
unnamed: C1605.1, K1604.4, L1601.2
unnamed: C1606.1, K1602.4, L1602.1
unnamed: C1607.1, K1603.4, L1603.1
unnamed: C1608.1, K1605.4, L1604.1
unnamed: C1609.1, K1601.4, L1605.1
unnamed: C1610.1, C1615.1, L1605.2, L1611.1
unnamed: C1611.1, C1616.1, L1607.2, L1609.1
unnamed: C1612.1, C1617.1, L1603.2, L1612.1
unnamed: C1613.1, C1618.1, L1606.1, L1608.2
unnamed: C1614.1, C1619.1, L1604.2, L1610.1
unnamed: C1620.1, C1623.1, L1611.2, L1615.1
unnamed: C1621.1, C1624.1, L1609.2, L1614.1
unnamed: C1622.1, C1626.1, L1610.2, L1616.1
unnamed: C1625.1, C1628.1, L1613.1, L1617.1
unnamed: C1627.1, C1629.1, L1612.2, L1619.1
unnamed: C1630.1, K1601.9, L1615.2
unnamed: C1631.1, K1605.9, L1616.2
unnamed: C1632.1, K1602.9, L1618.2
unnamed: C1633.1, K1604.9, L1620.2
unnamed: C1634.1, K1603.9, L1619.2
unnamed: C1804.1, C1805.1, L1801.2, R1801.2, R1803.2
unnamed: C1816.1, C1820.1, L1802.2, R1807.2, R1813.2
unnamed: C1817.1, C1821.1, L1803.2, R1809.2, R1814.2
unnamed: C2004.1, R2006.2
unnamed: C2110.1, K2109.4
unnamed: C2110.2, K2109.9
unnamed: C2113.1, K2108.4
unnamed: C2113.2, K2108.9
unnamed: C2114.1, K2107.4
unnamed: C2114.2, K2107.9
unnamed: C2115.2, R2104.2
unnamed: C2116.1, K2106.4
unnamed: C2116.2, K2106.9
unnamed: C2117.1, K2105.4
unnamed: C2117.2, K2105.9
unnamed: C2118.1, K2104.4
unnamed: C2118.2, K2104.9
unnamed: C2119.1, K2103.4
unnamed: C2119.2, K2103.9
unnamed: C2120.1, K2102.4
unnamed: C2120.2, K2102.9
unnamed: C2121.1, K2101.4
unnamed: C2121.2, K2101.9
unnamed: C2401.2, R2411.1, Y2401.3
unnamed: C2402.2, R2412.1, Y2401.1
unnamed: C2412.1, J2401.7
unnamed: C2006.1, C2007.1, D2001.2 (A), D2002.2 (A), IC2001.7 (DRVCC), U2001.1 (S), U2001.2 (S), U2001.3 (S)
unnamed: C2009.1, D2001.1 (K), IC2001.22 (BOOST2)
unnamed: C2010.2, D2002.1 (K), IC2001.36 (BOOST1)
unnamed: C2109.1, D2101.1 (K_1), J2101.A4 (VBUS_1), J2101.A9 (VBUS_2), J2101.B4 (VBUS_3), J2101.B9 (VBUS_4), Q2101.1 (S), Q2101.2 (S), Q2101.3 (S), R2101.1, R2102.1, U2103.24 (VDD)
unnamed: FB301.2, L301.1
unnamed: C2008.1, IC2001.3 (DRVSET), IC2001.8 (V5), IC2001.15 (MODE)
unnamed: IC2001.17 (FREQ), R2007.1
unnamed: C2002.1, IC2001.13 (ITH), R2006.1
unnamed: IC2001.6 (NDRV), U2001.4 (G)
unnamed: C2012.2, IC2001.34 (VIN), R2014.2
unnamed: IC2001.2 (VINOV), R2001.2, R2002.1
unnamed: IC2001.32 (VINSNS), R2012.2
unnamed: IC2001.30 (VOUTSNS), R2013.1
unnamed: C502.2, J501.1 (In)
unnamed: J2401.12, R2418.1
unnamed: J2401.14, R2419.1
unnamed: K501.3, R501.1
unnamed: K1701.4, L1708.1
unnamed: K1701.9, L1708.2
unnamed: K1702.4, L1707.1
unnamed: K1702.9, L1707.2
unnamed: K1703.4, L1706.1
unnamed: K1703.9, L1706.2
unnamed: K1704.4, L1705.1
unnamed: K1704.9, L1705.2
unnamed: K1705.4, L1704.1
unnamed: K1705.9, L1704.2
unnamed: K1706.4, L1703.1
unnamed: K1706.9, L1703.2
unnamed: K1707.4, L1702.1
unnamed: K1707.9, L1702.2
unnamed: K1708.4, L1701.1
unnamed: K1708.9, L1701.2
unnamed: L402.2, R401.1
unnamed: L1601.1, L1606.2
unnamed: L1602.2, L1607.1
unnamed: L1608.1, L1613.2
unnamed: L1614.2, L1618.1
unnamed: L1617.2, L1620.1
unnamed: Q2001.4 (G), R2017.2
unnamed: Q2002.4 (G), R2018.2
unnamed: Q2002.1 (S), Q2002.2 (S), Q2002.3 (S), Q2004.1 (S), Q2004.2 (S), Q2004.3 (S), R2021.4
unnamed: Q2003.4 (G), R2022.2
unnamed: Q2004.4 (G), R2023.2
unnamed: C2115.1, Q2101.5 (D), R2105.2, R2106.1
unnamed: Q2101.4 (G), R2102.2, R2103.1, R2104.1
unnamed: C2305.1, Q2301.3 (D), U2301.12 (HB)
unnamed: Q2301.1 (G), Q2304.1 (G), Q2304.5 (G), U2301.8 (LO)
unnamed: C2306.1, Q2302.3 (D), U2302.12 (HB)
unnamed: Q2302.1 (G), Q2306.1 (G), Q2306.5 (G), U2302.8 (LO)
unnamed: C2305.2, Q2303.3 (S), Q2303.4 (S), Q2303.6 (S), Q2303.7 (S), Q2303.8 (S), Q2303.9 (S), Q2303.10 (S), Q2303.11 (S), Q2303.12 (S), Q2304.2 (D), T2301.1, U2301.9 (HS), U2301.13 (HS), U2301.14 (HS), U2301.16 (HS), U2301.21 (HS_DAP)
unnamed: Q2304.3 (S), Q2304.4 (S), Q2304.6 (S), Q2304.7 (S), Q2304.8 (S), Q2304.9 (S), Q2304.10 (S), Q2304.11 (S), Q2304.12 (S)
unnamed: C2306.2, Q2305.3 (S), Q2305.4 (S), Q2305.6 (S), Q2305.7 (S), Q2305.8 (S), Q2305.9 (S), Q2305.10 (S), Q2305.11 (S), Q2305.12 (S), Q2306.2 (D), T2301.2, U2302.9 (HS), U2302.13 (HS), U2302.14 (HS), U2302.16 (HS), U2302.21 (HS_DAP)
unnamed: Q2306.3 (S), Q2306.4 (S), Q2306.6 (S), Q2306.7 (S), Q2306.8 (S), Q2306.9 (S), Q2306.10 (S), Q2306.11 (S), Q2306.12 (S)
unnamed: R301.1, R302.2, R303.2
unnamed: R502.1, T501.5
unnamed: R504.1, T501.4
unnamed: R802.1, R803.1, R804.1
unnamed: R902.1, R903.1, R904.1
unnamed: R1002.1, R1003.1, R1004.1
unnamed: R1102.1, R1103.1, R1104.1
unnamed: R2015.2, R2019.2, R2021.3
unnamed: R2016.2, R2020.2, R2021.2
unnamed: T301.4 (OUT1A), U302.3 (J2)
unnamed: C304.2, R304.2, T301.3 (OUT1B), T301.5 (OUT2B), T301.7 (OUT2B)
unnamed: TP201.1, U201.56 (PG0)
unnamed: TP202.1, U201.57 (PG1)
unnamed: TP203.1, U201.87 (PG2)
unnamed: TP204.1, U201.88 (PG3)
unnamed: TP205.1, U201.89 (PG4)
unnamed: TP206.1, U201.90 (PG5)
unnamed: TP207.1, U201.91 (PG6)
unnamed: TP208.1, U201.92 (PG7)
unnamed: TP209.1, U201.93 (PG8)
unnamed: TP210.1, U201.129 (PG14)
unnamed: TP211.1, U201.132 (PG15)
unnamed: C215.1, U201.71 (VCAP1)
unnamed: C213.1, U201.106 (VCAP2)
unnamed: C302.1, R303.1, U301.3 (+)
unnamed: FB301.1, U301.1, U301.2 (-)
unnamed: T301.6 (OUT2A), U303.3 (J2)
unnamed: T301.8 (OUT2A), U304.3 (J2)
unnamed: C318.2, C319.2, U306.27 (VDD18)
unnamed: C403.1, U410.5 (J1)
unnamed: C404.1, U411.5 (J1)
unnamed: C405.1, U412.5 (J1)
unnamed: C406.1, U413.5 (J1)
unnamed: C407.1, U414.5 (J1)
unnamed: U415.5 (J1), U418.1 (J3), U421.3 (J2)
unnamed: C409.1, U416.5 (J1)
unnamed: C411.1, U417.5 (J1)
unnamed: L402.1, U418.5 (J1)
unnamed: C414.1, U419.5 (J1)
unnamed: L403.1, U420.5 (J1)
unnamed: L403.2, U421.5 (J1)
unnamed: C416.1, U422.5 (J1)
unnamed: L404.1, U423.5 (J1)
unnamed: C418.1, U424.5 (J1)
unnamed: L405.1, U425.5 (J1)
unnamed: C421.1, U426.5 (J1)
unnamed: R601.2, U601.3 (EN)
unnamed: C604.1, U601.1 (OUT), U602.24 (VPP_2V5)
unnamed: U602.44 (IOB_3b_G6), Y601.3 (OUTPUT)
unnamed: C607.2, C609.2, R602.2, U602.29 (VCCPLL)
unnamed: R802.2, U801.3 (J2)
unnamed: U801.1 (J3), U802.1 (J3)
unnamed: R804.2, U802.3 (J2)
unnamed: R902.2, U901.3 (J2)
unnamed: U901.1 (J3), U902.1 (J3)
unnamed: R904.2, U902.3 (J2)
unnamed: R1002.2, U1001.3 (J2)
unnamed: U1001.1 (J3), U1002.1 (J3)
unnamed: R1004.2, U1002.3 (J2)
unnamed: R1102.2, U1101.3 (J2)
unnamed: U1101.1 (J3), U1102.1 (J3)
unnamed: R1104.2, U1102.3 (J2)
unnamed: C1207.1, C1214.1, R1203.1, U1202.2 (COM1)
unnamed: C1208.1, C1211.1, R1204.1, U1202.4 (COM2)
unnamed: C1204.1, C1206.1, R1201.1, U1202.9 (COM3)
unnamed: C1203.1, C1205.1, R1202.1, U1202.10 (COM4)
unnamed: C1207.2, U1203.5 (INA+)
unnamed: C1204.2, U1203.4 (INA-)
unnamed: R1205.2, R1206.1, U1203.7 (INB)
unnamed: R1205.1, R1209.1, U1203.8 (OUTA)
unnamed: R1206.2, R1210.1, U1203.6 (OUTB)
unnamed: C1208.2, U1204.5 (INA+)
unnamed: C1205.2, U1204.4 (INA-)
unnamed: R1207.2, R1208.1, U1204.7 (INB)
unnamed: R1207.1, R1211.1, U1204.8 (OUTA)
unnamed: R1208.2, R1212.1, U1204.6 (OUTB)
unnamed: C1307.1, C1314.1, R1303.1, U1302.2 (COM1)
unnamed: C1308.1, C1311.1, R1304.1, U1302.4 (COM2)
unnamed: C1304.1, C1306.1, R1301.1, U1302.9 (COM3)
unnamed: C1303.1, C1305.1, R1302.1, U1302.10 (COM4)
unnamed: C1307.2, U1303.5 (INA+)
unnamed: C1304.2, U1303.4 (INA-)
unnamed: R1305.2, R1306.1, U1303.7 (INB)
unnamed: R1305.1, R1309.1, U1303.8 (OUTA)
unnamed: R1306.2, R1310.1, U1303.6 (OUTB)
unnamed: C1308.2, U1304.5 (INA+)
unnamed: C1305.2, U1304.4 (INA-)
unnamed: R1307.2, R1308.1, U1304.7 (INB)
unnamed: R1307.1, R1311.1, U1304.8 (OUTA)
unnamed: R1308.2, R1312.1, U1304.6 (OUTB)
unnamed: C1407.1, C1414.1, R1403.1, U1402.2 (COM1)
unnamed: C1408.1, C1411.1, R1404.1, U1402.4 (COM2)
unnamed: C1404.1, C1406.1, R1401.1, U1402.9 (COM3)
unnamed: C1403.1, C1405.1, R1402.1, U1402.10 (COM4)
unnamed: C1407.2, U1403.5 (INA+)
unnamed: C1404.2, U1403.4 (INA-)
unnamed: R1405.2, R1406.1, U1403.7 (INB)
unnamed: R1405.1, R1409.1, U1403.8 (OUTA)
unnamed: R1406.2, R1410.1, U1403.6 (OUTB)
unnamed: C1408.2, U1404.5 (INA+)
unnamed: C1405.2, U1404.4 (INA-)
unnamed: R1407.2, R1408.1, U1404.7 (INB)
unnamed: R1407.1, R1411.1, U1404.8 (OUTA)
unnamed: R1408.2, R1412.1, U1404.6 (OUTB)
unnamed: K1601.12, U1601.3 (DRAIN0)
unnamed: K1602.12, U1601.4 (DRAIN1)
unnamed: K1603.12, U1601.5 (DRAIN2)
unnamed: K1604.12, U1601.6 (DRAIN3)
unnamed: K1605.12, U1601.11 (DRAIN4)
unnamed: K1701.12, U1701.3 (DRAIN0)
unnamed: K1702.12, U1701.4 (DRAIN1)
unnamed: K1703.12, U1701.5 (DRAIN2)
unnamed: K1704.12, U1701.6 (DRAIN3)
unnamed: K1705.12, U1701.11 (DRAIN4)
unnamed: K1706.12, U1701.12 (DRAIN5)
unnamed: K1707.12, U1701.13 (DRAIN6)
unnamed: K1708.12, U1701.14 (DRAIN7)
unnamed: C1803.1, U1801.6 (BOOT)
unnamed: C1803.2, L1801.1, U1801.5 (SW)
unnamed: CF1801.1, U1801.7 (VCC)
unnamed: R1801.1, R1802.2, U1801.8 (VOUT_FB)
unnamed: C1811.1, R1804.2, U1802.1 (OUT)
unnamed: C1814.1, U1803.6 (CB)
unnamed: R1807.1, R1808.2, U1803.4 (FB)
unnamed: C1814.2, L1802.1, U1803.2 (SW)
unnamed: C1815.1, U1804.6 (CB)
unnamed: R1809.1, R1810.2, U1804.4 (FB)
unnamed: C1815.2, L1803.1, U1804.2 (SW)
unnamed: R1805.2, U1805.3 (EN)
unnamed: C1818.1, R1811.2, U1805.1 (OUT)
unnamed: R1806.2, U1806.3 (EN)
unnamed: C1819.1, R1812.2, U1806.1 (OUT)
unnamed: R2009.1, R2010.2, U2002.3 (+)
unnamed: C2011.1, R2008.2, R2011.1, U2002.2 (-)
unnamed: R2003.1, R2004.2, U2002.5 (+)
unnamed: K2101.12, U2101.3 (DRAIN0)
unnamed: K2102.12, U2101.4 (DRAIN1)
unnamed: K2103.12, U2101.5 (DRAIN2)
unnamed: K2104.12, U2101.6 (DRAIN3)
unnamed: K2105.12, U2101.11 (DRAIN4)
unnamed: K2106.12, U2101.12 (DRAIN5)
unnamed: K2107.12, U2101.13 (DRAIN6)
unnamed: K2108.12, U2101.14 (DRAIN7)
unnamed: U2101.9 (SER_OUT), U2102.2 (SER_IN)
unnamed: K2109.12, U2102.3 (DRAIN0)
unnamed: R2106.2, U2103.9 (DISCH)
unnamed: R2103.2, U2103.16 (VBUS_EN_SNK)
unnamed: C2111.1, U2103.21 (VREG_1V2)
unnamed: Q2303.1 (G), Q2303.5 (G), U2301.10 (HO)
unnamed: Q2305.1 (G), Q2305.5 (G), U2302.10 (HO)
unnamed: R2405.2, R2408.1, U2401.11 (CRS_DV/MODE2)
unnamed: R2415.2, U2401.24 (RBIAS)
unnamed: R2403.2, R2410.1, U2401.8 (RXD0/MODE0)
unnamed: R2404.2, R2409.1, U2401.7 (RXD1/MODE1)
unnamed: R2401.2, U2401.10 (RXER/PHYAD0)
unnamed: C2406.1, C2407.1, C2408.1, C2409.1, FB2401.2, R2413.1, R2414.1, R2416.1, R2417.1, U2401.1 (VDD2A), U2401.19 (VDD1A), U2402.5 (VBUS)
unnamed: C2404.1, C2405.1, U2401.6 (VDDCR)
unnamed: R2411.2, U2401.5 (XTAL1/CLKIN)
unnamed: R2412.2, U2401.4 (XTAL2)
unnamed: R2402.2, R2406.1, U2401.14 (~INT/REFCLKO)
unnamed: R209.1, Y201.3 (OUTPUT)
unnamed: R203.2, Y201.1 (TRI-STATE)
VBUS: C1801.1, C1802.1, C1807.1, C1808.1, C1809.1, C1810.1, C2014.1, C2015.1, C2017.1, C2018.1, C2019.1, C2020.1, C2022.1, D2101.3 (K_2), Q2001.5 (D), R2012.1, R2014.1, R2105.1, U1801.4 (VIN), U1803.3 (VIN), U1803.5 (EN), U1804.3 (VIN), U2001.5 (D), U2001.6 (D), U2001.7 (D), U2001.8 (D)
Veer: C2021.1, C2023.1, Q2003.5 (D), Q2303.2 (D), Q2305.2 (D), R2001.1, R2003.2, R2009.2, R2013.2
nRESET: J202.10 (~RESET), U201.25 (NRST), U401.18 (~RESET), U2401.15 (~RST)
